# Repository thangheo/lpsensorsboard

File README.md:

# low power sensorsboard
một mạng cảm biến tự làm chạy bằng pin với nhiều loại cảm biến cho nhà thông minh.
PCB và sơ đồ được thiết kế bằng Kicad 6.0.
một phần của cấu hình firmare được tạo bởi STM CubeMX.

Ở phiên bản hiện tại, các cảm biến được hỗ trợ là Cường độ ánh sáng sử dụng điện trở quang (ánh sáng rất yếu, <5 Lux),
Cảm biến CO2/độ ẩm/nhiệt độ từ sensirion SCD41(từ Seeedstudio
với đầu nối Grove), cảm biến âm thanh (Micrô), cảm biến CO/NH3, cảm biến AM2320 cho độ ẩm và nhiệt độ.
Tôi chưa thử nghiệm trên phần cứng thực vì tôi chỉ thiết kế PCB và lập trình Firmware vài tuần trước.
Vi điều khiển là STM32L051 với lõi Cortex M0+, ở chế độ STANDBY, mức tiêu thụ điện năng có thể giảm xuống mức thấp nhất là vài micro amp.
Theo tính toán của tôi, thiết bị có thể chạy tới 7-8 tháng với thời gian đo 2 phút với
 Pin Lithium 18658 (1000mAh). Nếu không có cảm biến CO/NH3, nó có thể chạy tới nhiều năm mà không cần sạc lại
  pin vì cảm biến này tiêu thụ một nửa năng lượng (35mA trong tổng số 70mA).

1. Cấu trúc dữ liệu gửi đi (bổ sung sau)

typedef struct {
  unsigned int temperature;
  unsigned int humidity;
  unsigned int AM2320_temperature;
  unsigned int AM2320_humidity;
  unsigned int audio;
  unsigned int light;
  unsigned int CO2;
  unsigned int NH3;
}

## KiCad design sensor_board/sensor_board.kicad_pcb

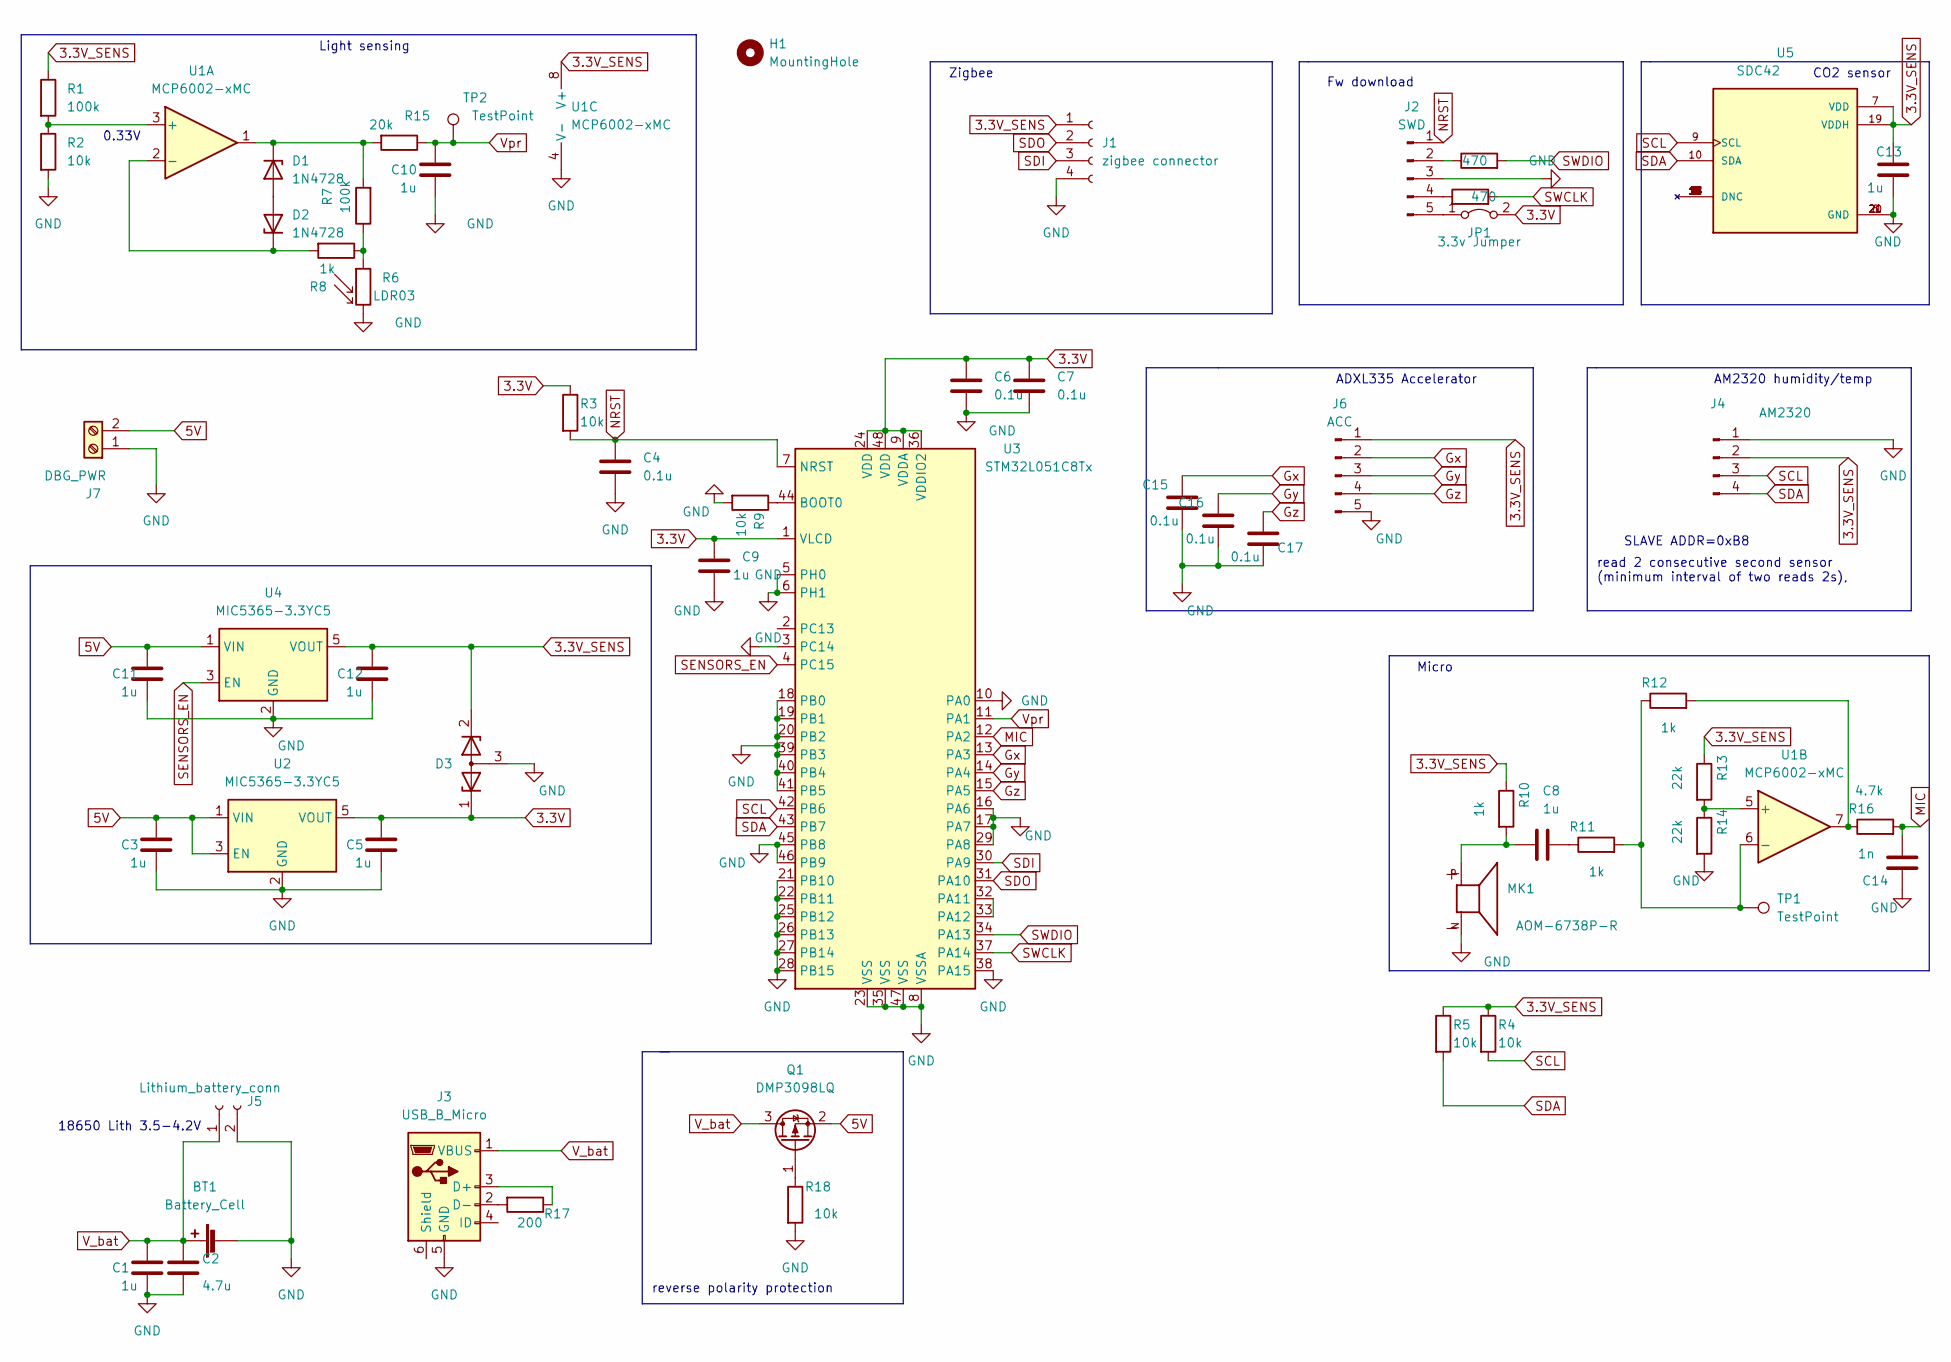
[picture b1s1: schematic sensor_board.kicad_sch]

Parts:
BT1: Battery_Cell; BatteryHolder_MPD_BH-18650-PC2
C1, C3, C5, C8, C9, C10, C11, C12, C13: 1u; C_1206_3216Metric_Pad1.33x1.80mm_HandSolder
C2: 4.7u; C_1206_3216Metric_Pad1.33x1.80mm_HandSolder
C4, C6, C7, C15, C16, C17: 0.1u; C_1206_3216Metric_Pad1.33x1.80mm_HandSolder
C14: 1n; C_1206_3216Metric_Pad1.33x1.80mm_HandSolder
D1, D2: 1N4728; D_SOD-110
D3: D_Zener_Dual_CommonAnode_KKA; SOT-23
H1: MountingHole; MountingHole_2.7mm_M2.5_Pad
J1: zigbee connector; PinSocket_1x04_P2.54mm_Vertical
J2: SWD; PinSocket_1x05_P2.54mm_Vertical
J3: USB_B_Micro; USB_Micro-B_Wuerth_629105150521
J4: AM2320; PinSocket_1x04_P2.54mm_Vertical
J5: Lithium_battery_conn; PinHeader_1x02_P1.27mm_Vertical
J6: ACC; PinSocket_1x05_P2.54mm_Vertical
J7: DBG_PWR; TerminalBlock_bornier-2_P5.08mm
JP1: 3.3v Jumper; PinSocket_1x02_P1.27mm_Vertical
MK1: AOM-6738P-R; MIC_AOM-6738P-R; PARTREV B
Q1: DMP3098LQ; SOT-23
R1, R7: 100k; R_0805_2012Metric_Pad1.20x1.40mm_HandSolder
R2, R3, R4, R5, R9, R18: 10k; R_0805_2012Metric_Pad1.20x1.40mm_HandSolder
R6: LDR03; R_LDR_10x8.5mm_P7.6mm_Vertical
R8, R10, R11, R12: 1k; R_0805_2012Metric_Pad1.20x1.40mm_HandSolder
R13, R14: 22k; R_0805_2012Metric_Pad1.20x1.40mm_HandSolder
R15: 20k; R_0805_2012Metric_Pad1.20x1.40mm_HandSolder
R16: 4.7k; R_0805_2012Metric_Pad1.20x1.40mm_HandSolder
R17: 200; R_0805_2012Metric_Pad1.20x1.40mm_HandSolder
R19, R20: 470; R_0805_2012Metric_Pad1.20x1.40mm_HandSolder
TP1, TP2: TestPoint; TestPoint_Loop_D2.60mm_Drill1.6mm_Beaded
U1: MCP6002-xMC; DFN-8-1EP_3x2mm_P0.5mm_EP1.75x1.45mm
U2, U4: MIC5365-3.3YC5; SOT-353_SC-70-5
U3: STM32L051C8Tx; LQFP-48_7x7mm_P0.5mm
U5: SDC42; XDCR_SCD41-D-R2; PARTREV 1.2

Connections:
3.3V: C5.1, C6.1, C7.1, C9.1, D3.1 (K), JP1.2 (B), R3.1, U2.5 (VOUT), U3.1 (VLCD), U3.9 (VDDA), U3.24 (VDD), U3.36 (VDDIO2), U3.48 (VDD)
3.3V_SENS: C12.1, C13.1, D3.2 (K), J1.1, J4.2, J6.1, R1.1, R4.1, R5.1, R10.1, R13.1, U1.8 (V+), U4.5 (VOUT), U5.7 (VDD), U5.19 (VDDH)
5V: C3.1, C11.1, J7.2, Q1.2 (S), U2.1 (VIN), U2.3 (EN), U4.1 (VIN)
GND: BT1.2 (-), C1.2, C2.2, C3.2, C4.2, C5.2, C6.2, C7.2, C9.2, C10.2, C11.2, C12.2, C13.2, C14.1, C15.1, C16.1, C17.1, D3.3 (A), J1.4, J2.3, J3.5 (GND), J4.1, J5.2, J6.5, J7.1, MK1.N, R2.2, R6.2, R9.2, R14.2, R18.2, U1.4 (V-), U1.9 (V-), U2.2 (GND), U3.3 (PC14), U3.5 (PH0), U3.6 (PH1), U3.8 (VSSA), U3.10 (PA0), U3.16 (PA6), U3.17 (PA7), U3.18 (PB0), U3.19 (PB1), U3.20 (PB2), U3.21 (PB10), U3.22 (PB11), U3.23 (VSS), U3.25 (PB12), U3.26 (PB13), U3.27 (PB14), U3.28 (PB15), U3.29 (PA8), U3.35 (VSS), U3.38 (PA15), U3.39 (PB3), U3.40 (PB4), U3.41 (PB5), U3.45 (PB8), U3.46 (PB9), U3.47 (VSS), U4.2 (GND), U5.6 (GND), U5.20 (GND), U5.21 (GND)
Gx: C15.2, J6.2, U3.13 (PA3)
Gy: C16.2, J6.3, U3.14 (PA4)
Gz: C17.2, J6.4, U3.15 (PA5)
MIC: C14.2, R16.2, U3.12 (PA2)
NRST: C4.1, J2.1, R3.2, U3.7 (NRST)
unnamed: C8.1, MK1.P, R10.2
unnamed: C8.2, R11.1
unnamed: D1.1 (K), R7.2, R15.2, U1.1
unnamed: D1.2 (A), D2.2 (A)
unnamed: D2.1 (K), R8.2, U1.2 (-)
unnamed: J2.2, R20.1
unnamed: J2.4, R19.1
unnamed: J2.5, JP1.1 (A)
unnamed: J3.2 (D-), R17.2
unnamed: J3.3 (D+), R17.1
unnamed: Q1.1 (G), R18.1
unnamed: R1.2, R2.1, U1.3 (+)
unnamed: R6.1, R7.1, R8.1
unnamed: R9.1, U3.44 (BOOT0)
unnamed: R11.2, R12.1, TP1.1, U1.6 (-)
unnamed: R12.2, R16.1, U1.7
unnamed: R13.2, R14.1, U1.5 (+)
unnamed: U3.32 (PA11), U3.33 (PA12)
SCL: J4.3, R4.2, U3.42 (PB6), U5.9 (SCL)
SDA: J4.4, R5.2, U3.43 (PB7), U5.10 (SDA)
SDI: J1.3, U3.30 (PA9)
SDO: J1.2, U3.31 (PA10)
SENSORS_EN: U3.4 (PC15), U4.3 (EN)
SWCLK: R19.2, U3.37 (PA14)
SWDIO: R20.2, U3.34 (PA13)
V_bat: BT1.1 (+), C1.1, C2.1, J3.1 (VBUS), J5.1, Q1.3 (D)
Vpr: C10.1, R15.1, TP2.1, U3.11 (PA1)

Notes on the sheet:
read 2 consecutive second sensor (minimum interval of two reads 2s),
Zigbee
18650 Lith 3.5-4.2V
0.33V
ADXL335 Accelerator
CO2 sensor
Light sensing
reverse polarity protection
Micro
Fw download
AM2320 humidity/temp
SLAVE ADDR=0xB8

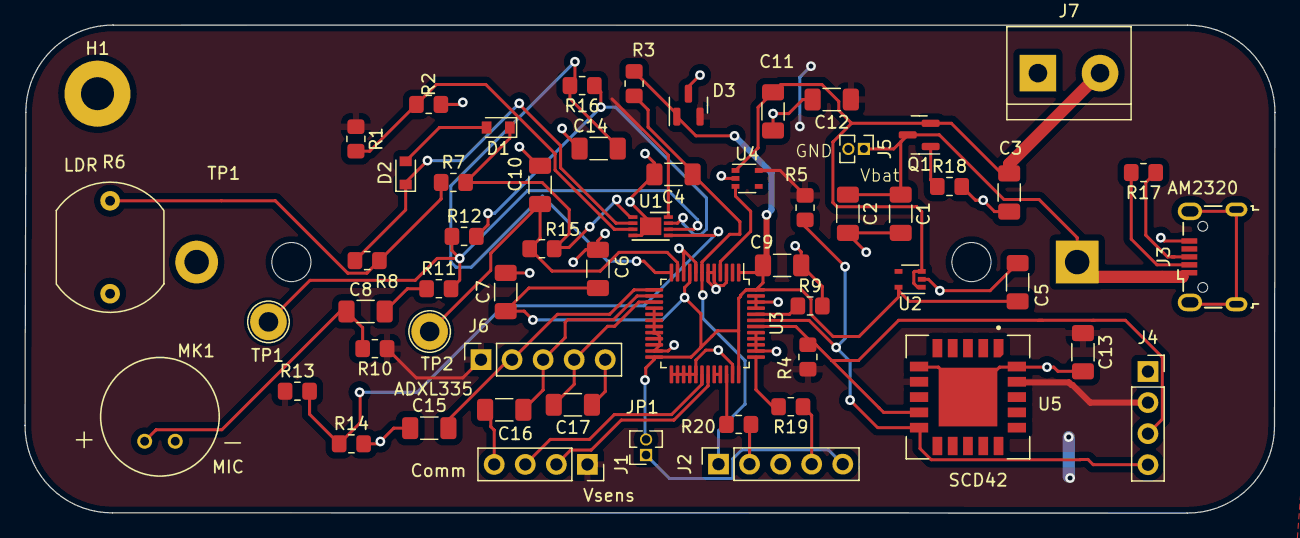
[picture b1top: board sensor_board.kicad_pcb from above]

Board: 2 copper layers, 102.2 x 39.9 mm, 59 parts (1 on the bottom side), 36 nets.

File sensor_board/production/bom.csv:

Designator,Footprint,Quantity,Value,LCSC Part #
BT1,BatteryHolder_MPD_BH-18650-PC2,1,Battery_Cell,
C1,1206,1,1u,
C10,1206,1,1u,
C11,1206,1,1u,
C12,1206,1,1u,
C13,1206,1,1u,
C14,1206,1,1n,
C2,1206,1,4.7u,
C3,1206,1,1u,
C4,1206,1,0.1u,
C5,1206,1,1u,
C6,1206,1,0.1u,
C7,1206,1,0.1u,
C8,1206,1,1u,
C9,1206,1,1u,
"D1, D2",D_SOD-110,2,1N4728,
D3,SOT-23,1,D_Zener_Dual_CommonAnode_KKA,
H1,MountingHole_2.7mm_M2.5_Pad,1,MountingHole,
J1,PinSocket_1x04_P2.54mm_Vertical,1,zigbee connector,
J2,PinSocket_1x05_P2.54mm_Vertical,1,SWD,
J3,USB_Micro-B_Wuerth_629105150521,1,USB_B_Micro,
J4,PinSocket_1x04_P2.54mm_Vertical,1,AM2320,
J5,PinHeader_1x02_P1.27mm_Vertical,1,Lithium_battery_conn,
J6,PinSocket_1x05_P2.54mm_Vertical,1,ACC,
J7,TerminalBlock_bornier-2_P5.08mm,1,DBG_PWR,
JP1,PinSocket_1x02_P1.27mm_Vertical,1,3.3v Jumper,
MK1,MIC_AOM-6738P-R,1,AOM-6738P-R,
Q1,SOT-23,1,DMP3098LQ,
R1,0805,1,100k,
R10,0805,1,1k,
R11,0805,1,1k,
R12,0805,1,1k,
R13,0805,1,22k,
R14,0805,1,22k,
R15,0805,1,20k,
R16,0805,1,4.7k,
R17,0805,1,200,
R18,0805,1,10k,
R19,0805,1,470,
R2,0805,1,10k,
R20,0805,1,470,
R3,0805,1,10k,
R4,0805,1,10k,
R5,0805,1,10k,
R6,R_LDR_10x8.5mm_P7.6mm_Vertical,1,LDR03,
R7,0805,1,100k,
R8,0805,1,1k,
R9,0805,1,10k,
"TP1, TP2",TestPoint_Loop_D2.60mm_Drill1.6mm_Beaded,2,TestPoint,
U1,DFN-8-1EP_3x2mm_P0.5mm_EP1.75x1.45mm,1,MCP6002-xMC,
"U2, U4",SOT-353_SC-70-5,2,MIC5365-3.3YC5,
U3,LQFP-48_7x7mm_P0.5mm,1,STM32L051C8Tx,
U5,XDCR_SCD41-D-R2,1,SDC42,

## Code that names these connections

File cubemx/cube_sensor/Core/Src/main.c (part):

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  /*Configure GPIO pin Output Level */
  HAL_GPIO_WritePin(GPIOC, GPIO_PIN_15, GPIO_PIN_RESET);

  /*Configure GPIO pin : PC14 */
  GPIO_InitStruct.Pin = GPIO_PIN_14;
  GPIO_InitStruct.Mode = GPIO_MODE_ANALOG;
  GPIO_InitStruct.Pull = GPIO_NOPULL;
  HAL_GPIO_Init(GPIOC, &GPIO_InitStruct);

  /*Configure GPIO pin : PC15 */
  GPIO_InitStruct.Pin = GPIO_PIN_15;
  GPIO_InitStruct.Mode = GPIO_MODE_OUTPUT_PP;
  GPIO_InitStruct.Pull = GPIO_NOPULL;
  GPIO_InitStruct.Speed = GPIO_SPEED_FREQ_LOW;
  HAL_GPIO_Init(GPIOC, &GPIO_InitStruct);

  /*Configure GPIO pins : PH0 PH1 */
  GPIO_InitStruct.Pin = GPIO_PIN_0|GPIO_PIN_1;
  GPIO_InitStruct.Mode = GPIO_MODE_ANALOG;
  GPIO_InitStruct.Pull = GPIO_NOPULL;
  HAL_GPIO_Init(GPIOH, &GPIO_InitStruct);

  /*Configure GPIO pins : PA0 PA3 PA4 PA5
                           PA6 PA7 PA8 PA11
                           PA12 PA15 */
  GPIO_InitStruct.Pin = GPIO_PIN_0|GPIO_PIN_3|GPIO_PIN_4|GPIO_PIN_5
                          |GPIO_PIN_6|GPIO_PIN_7|GPIO_PIN_8|GPIO_PIN_11
                          |GPIO_PIN_12|GPIO_PIN_15;
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  GPIO_InitStruct.Pull = GPIO_NOPULL;
  HAL_GPIO_Init(GPIOA, &GPIO_InitStruct);

  /*Configure GPIO pins : PB0 PB1 PB2 PB10
                           PB11 PB12 PB13 PB14
                           PB15 PB3 PB4 PB5
                           PB8 PB9 */
  GPIO_InitStruct.Pin = GPIO_PIN_0|GPIO_PIN_1|GPIO_PIN_2|GPIO_PIN_10
                          |GPIO_PIN_11|GPIO_PIN_12|GPIO_PIN_13|GPIO_PIN_14
                          |GPIO_PIN_15|GPIO_PIN_3|GPIO_PIN_4|GPIO_PIN_5
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
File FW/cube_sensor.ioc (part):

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Mcu.Name=STM32L051C(6-8)Tx
Mcu.Package=LQFP48
Mcu.UserName=STM32L051C8Tx
PA1.Mode=IN1
PA1.Signal=ADC_IN1
PA10.Mode=Asynchronous
PA10.Signal=USART1_RX
PA13.Mode=Serial_Wire
PA13.Signal=SYS_SWDIO
PA14.Mode=Serial_Wire
PA14.Signal=SYS_SWCLK
PA2.Mode=IN2
PA2.Signal=ADC_IN2
PA3.Mode=IN3
PA3.Signal=ADC_IN3
PA4.Mode=IN4
PA4.Signal=ADC_IN4
PA5.Mode=IN5
PA5.Signal=ADC_IN5
PA9.Mode=Asynchronous
PA9.Signal=USART1_TX
PB6.Mode=I2C
PB6.Signal=I2C1_SCL
PB7.Mode=I2C
PB7.Signal=I2C1_SDA
PC13.Mode=WakeUpAF1
PC13.Signal=RTC_OUT_ALARM
PC15-OSC32_OUT.Signal=GPIO_Output
RCC.HSE_VALUE=8000000
RCC.SYSCLKFreq_VALUE=16000000
RCC.SYSCLKSource=RCC_SYSCLKSOURCE_HSI
board=custom

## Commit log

2023-01-10 ignore kicad backup files
2023-01-10 add readme.txt
2023-01-10 modified: README.md
2023-01-10 remove files in gitignore
2023-01-10 add demo images
2023-01-10 remove .vscode
2023-01-11 replace 2 cells AA with single cell 18650 battery holder
2023-01-16 modified: sensor_board/sensor_board.kicad_pcb modified: sensor_board/sensor_board.kicad_sch Fix SDI pins wiring error
2023-01-17 1. modify schematic, replace mosfet which control sensors power with LDO IC 2. add accelerator sensor to measure wind speed 3. ..
2023-01-20 1. use sensorion scd42 for lower power 2. add usb micro B for testing or using with backup battery later 3. add signal RC filter
2023-01-20 edit file name and images
2023-01-20 add image
2023-01-21 1.support FreeRTOS instead of round Robin task scheduling and remove unuse file 2. Fix scd42 task which (maybe) was wrong in implementation inherrited from Sensirion demo app
2023-01-21 1. add event group 2. add data transfer
2023-01-22 add reverse polarity protection mosfet and diode
2023-01-23 add sensor ID
2023-01-23 1. add acceleration sensor and fix warning
2023-01-26 add testpoints
2023-02-10 add cap to ..

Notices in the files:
cubemx/cube_sensor/Core/Src/main.c:
Copyright (c) 2023 STMicroelectronics.
All rights reserved.
This software is licensed under terms that can be found in the LICENSE file
